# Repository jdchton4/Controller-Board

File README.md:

# Controller-Board
Custom controller board for interfacing with ESP-32 projects

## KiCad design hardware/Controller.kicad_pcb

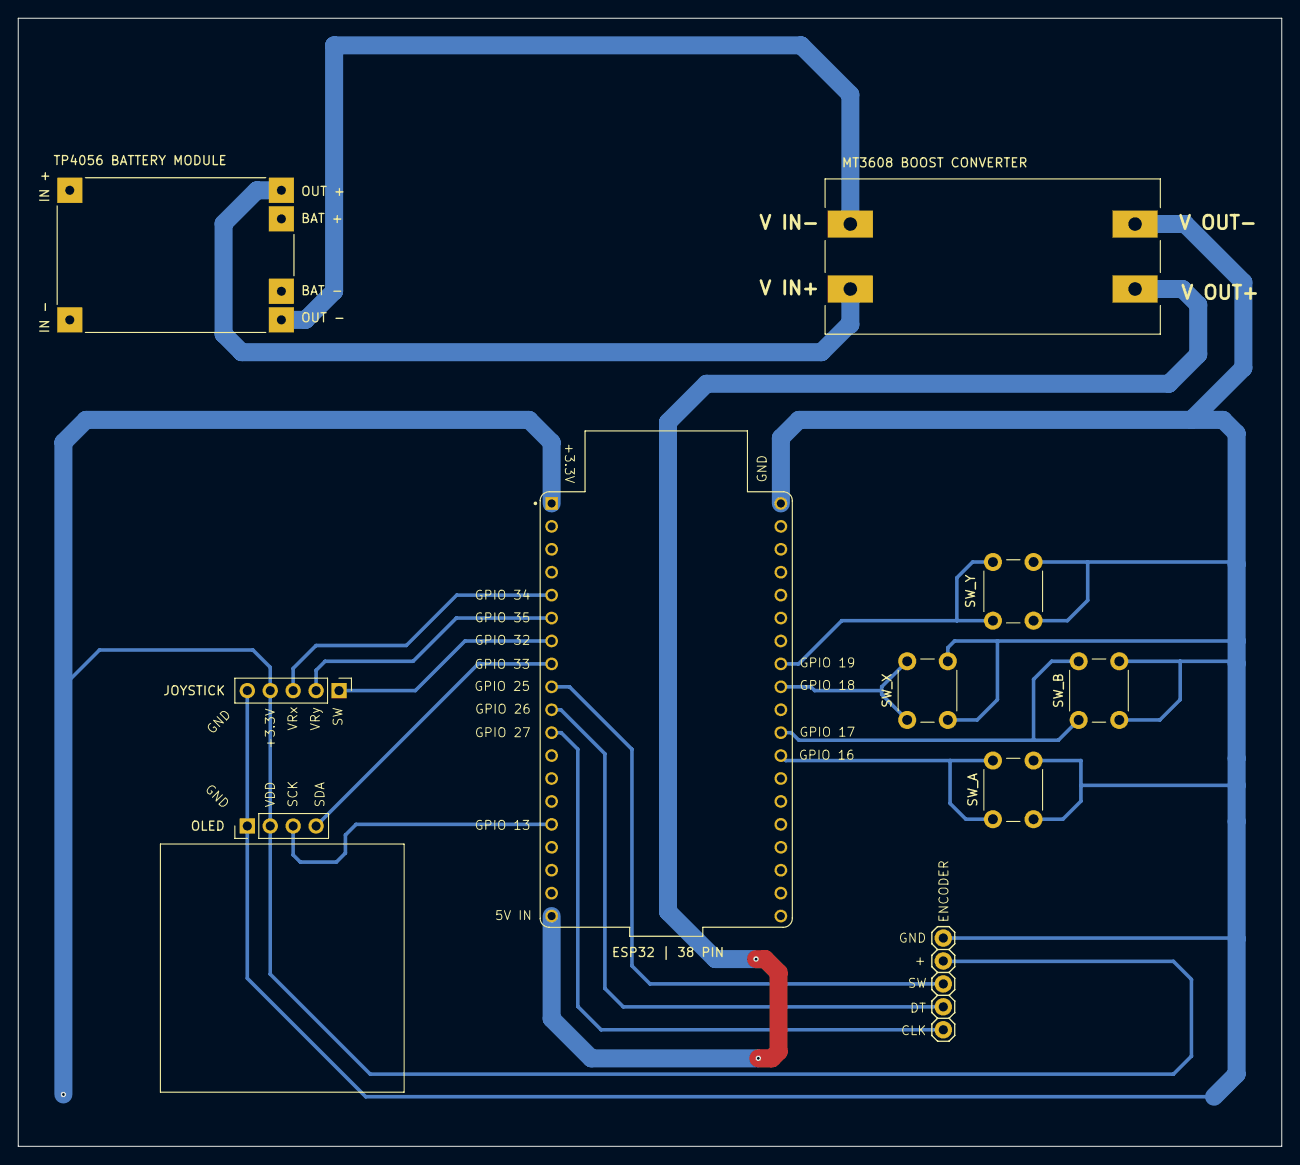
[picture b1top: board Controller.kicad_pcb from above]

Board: 2 copper layers, 140.0 x 125.0 mm, 10 parts (0 on the bottom side), 17 nets.

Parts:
ENCODER: KY-040; KY-040-PORT
ESP32 | 38 PIN: ESP32-DEVKITC-32E; MODULE_ESP32-DEVKITC-32E
JOYSTICK: Conn_01x05_Pin; PinHeader_1x05_P2.54mm_Vertical
MT3608 BOOST CONVERTER: MT3608_DC-DC_STEP_UP_CONVERTER_2A_BOOSTER_MODULE; MODULE_MT3608_DC-DC_STEP_UP_CONVERTER_2A_BOOSTER_MODULE
OLED: OLED; PinHeader_1x04_P2.54mm_Vertical
SW_A: SW_Push; SW_PUSH_6mm
SW_B: SW_Push; SW_PUSH_6mm
SW_X: SW_Push; SW_PUSH_6mm
SW_Y: SW_Push; SW_PUSH_6mm
TP4056 BATTERY MODULE: TP4056_MICRO-USB_CHARGER_-_1A; MODULE_TP4056_MICRO-USB_CHARGER_-_1A

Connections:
+3.3V: ENCODER.VCC, ESP32 | 38 PIN.J2_1 (3V3), JOYSTICK.4, OLED.2 (VCC)
/SW: ESP32 | 38 PIN.J2_7 (IO32), JOYSTICK.1
/VRx: ESP32 | 38 PIN.J2_5 (IO34), JOYSTICK.3
/VRy: ESP32 | 38 PIN.J2_6 (IO35), JOYSTICK.2
GND: ENCODER.GND, ESP32 | 38 PIN.J3_1 (GND_J3_1), JOYSTICK.5, MT3608 BOOST CONVERTER.VOUT_N (VOUT-), OLED.1 (GND), SW_A.2, SW_B.2, SW_X.2, SW_Y.2
unnamed: ESP32 | 38 PIN.J2_15 (IO13), OLED.3 (SCK)
unnamed: ESP32 | 38 PIN.J2_8 (IO33), OLED.4 (SDA)
unnamed: ESP32 | 38 PIN.J2_19 (EXT_5V), MT3608 BOOST CONVERTER.VOUT_P (VOUT+)
unnamed: ESP32 | 38 PIN.J3_12 (IO16), SW_A.1
unnamed: ESP32 | 38 PIN.J3_11 (IO17), SW_B.1
unnamed: ESP32 | 38 PIN.J3_9 (IO18), SW_X.1
unnamed: ESP32 | 38 PIN.J3_8 (IO19), SW_Y.1
unnamed: ENCODER.SW, ESP32 | 38 PIN.J2_9 (IO25)
unnamed: ENCODER.DT, ESP32 | 38 PIN.J2_10 (IO26)
unnamed: ENCODER.CLK, ESP32 | 38 PIN.J2_11 (IO27)
unnamed: MT3608 BOOST CONVERTER.VIN_P (VIN+), TP4056 BATTERY MODULE.OUT_P (OUT+)
unnamed: MT3608 BOOST CONVERTER.VIN_N (VIN-), TP4056 BATTERY MODULE.OUT_N (OUT-)

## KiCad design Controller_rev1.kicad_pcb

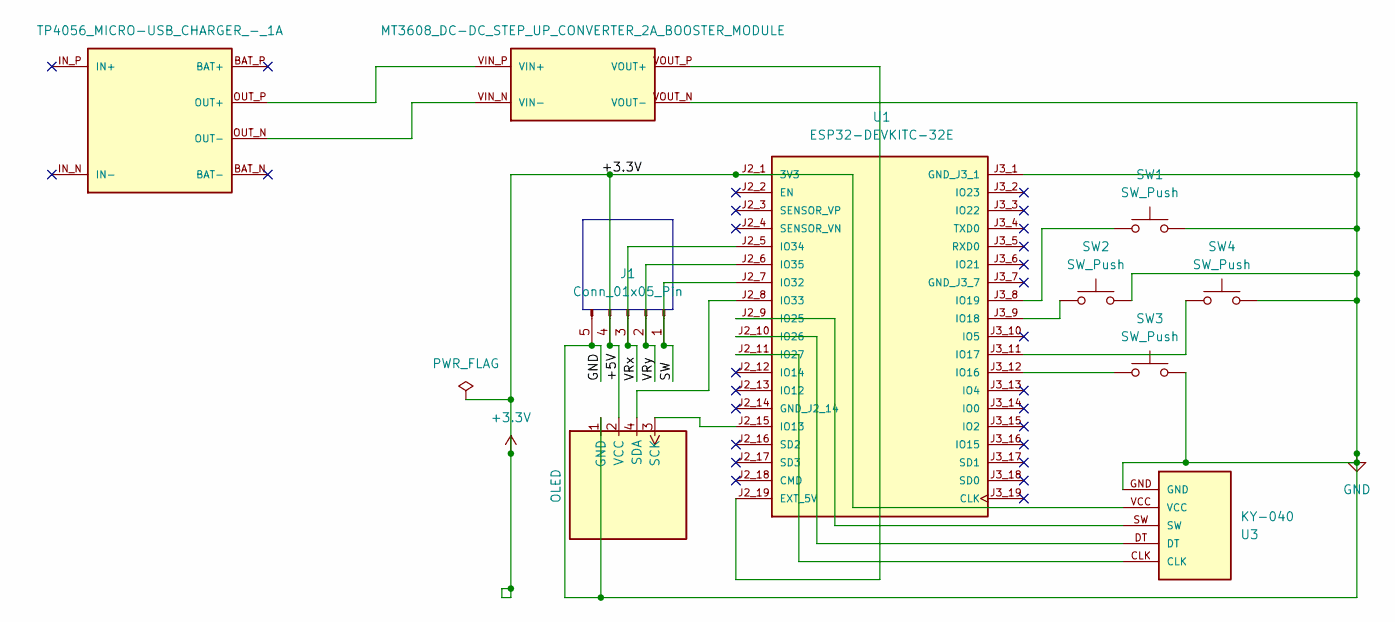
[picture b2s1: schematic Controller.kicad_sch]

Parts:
J1: Conn_01x05_Pin; PinHeader_1x05_P2.54mm_Vertical
OLED1: OLED; PinHeader_1x04_P2.54mm_Vertical
SW1, SW2, SW3, SW4: SW_Push; SW_PUSH-12mm
U1: ESP32-DEVKITC-32E; MODULE_ESP32-DEVKITC-32E; PARTREV 1.4
U2: MT3608_DC-DC_STEP_UP_CONVERTER_2A_BOOSTER_MODULE; MODULE_MT3608_DC-DC_STEP_UP_CONVERTER_2A_BOOSTER_MODULE
U3: KY-040; KY-040-PORT
U4: TP4056_MICRO-USB_CHARGER_-_1A; MODULE_TP4056_MICRO-USB_CHARGER_-_1A

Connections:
+3.3V: J1.4, OLED1.2 (VCC), U1.J2_1 (3V3), U3.VCC; also elsewhere on the board
/SW: J1.1, U1.J2_7 (IO32)
/VRx: J1.3, U1.J2_5 (IO34)
/VRy: J1.2, U1.J2_6 (IO35)
GND: J1.5, OLED1.1 (GND), SW1.2, SW2.2, SW3.2, SW4.2, U1.J3_1 (GND_J3_1), U2.VOUT_N (VOUT-), U3.GND; also elsewhere on the board
unnamed 5: OLED1.3 (SCK), U1.J2_15 (IO13); also elsewhere on the board
unnamed 6: OLED1.4 (SDA), U1.J2_8 (IO33); also elsewhere on the board
unnamed: U1.J2_19 (EXT_5V), U2.VOUT_P (VOUT+)
unnamed: SW3.1, U1.J3_12 (IO16)
unnamed: SW4.1, U1.J3_11 (IO17)
unnamed: SW2.1, U1.J3_9 (IO18)
unnamed: SW1.1, U1.J3_8 (IO19)
unnamed: U1.J2_9 (IO25), U3.SW
unnamed: U1.J2_10 (IO26), U3.DT
unnamed: U1.J2_11 (IO27), U3.CLK
unnamed: U2.VIN_P (VIN+), U4.OUT_P (OUT+)
unnamed: U2.VIN_N (VIN-), U4.OUT_N (OUT-)

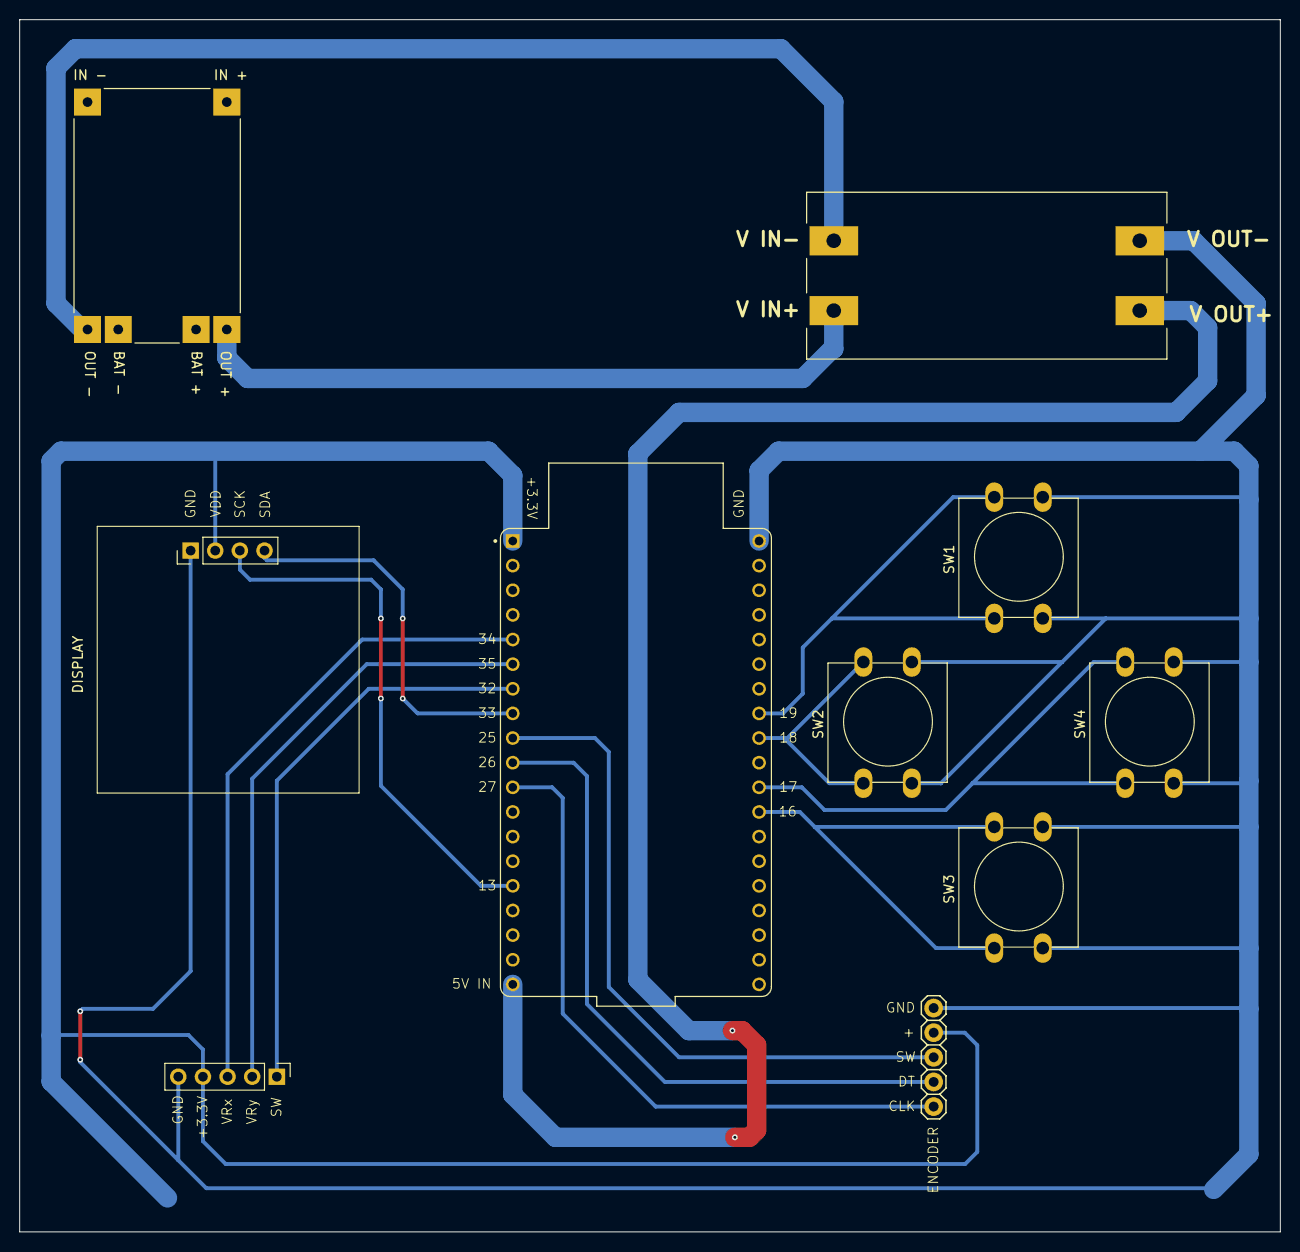
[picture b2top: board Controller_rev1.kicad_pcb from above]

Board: 2 copper layers, 130.0 x 125.0 mm, 10 parts (0 on the bottom side), 17 nets.

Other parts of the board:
DISPLAY: OLED; PinHeader_1x04_P2.54mm_Vertical

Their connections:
+3.3V: DISPLAY.2 (VCC); also elsewhere on the board
GND: DISPLAY.1 (GND); also elsewhere on the board
unnamed 5: DISPLAY.3 (SCK); also elsewhere on the board
unnamed 6: DISPLAY.4 (SDA); also elsewhere on the board
